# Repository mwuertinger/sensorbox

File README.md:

# Sensorbox

ESP8266 powered CO2, temperature, humidity and pressure sensor.

Displays the measurements on an OLED display and shows CO2 levels with green, yellow and red LEDs.
Measurements are sent via HTTPS to the [server](server/) which writes them to InfluxDB.
Alerting (temperature and battery) is handled by [temperature-alert](https://github.com/mwuertinger/temperature-alert).

## Software
The firmware is written in C++ and built using platformio. The server and config-tool are written in Go.

Generating protobuf code (required before building anything):
```
pip install nanopb==0.4.9.1 grpcio-tools
go install google.golang.org/protobuf/cmd/protoc-gen-go@latest
./protoc.sh
```

Building the firmware:
```
cd firmware
platformio run
```

Installing to a board connected via USB:
```
platformio run --target upload
```

### Configuration
The configuration is stored in flash and created with the [config-tool](config-tool/):
```
cd config-tool
go run ./generate -out config.bin -dev_id 1 -wlan_ssid ... -wlan_passwd ... -auth_token ... \
  -server_uri https://192.168.178.2:4000/sensorbox -server_fingerprint <sha1 of server cert> -bme280
esptool.py --port /dev/ttyUSB0 write_flash 0x03fb000 config.bin
```

The SHA1 fingerprint of the server certificate can be obtained with:
```
openssl x509 -in sensorbox-server.crt -noout -fingerprint -sha1
```
Devices with a fingerprint reject any other certificate, so reflash their config when the server certificate changes.

## Hardware
The PCB was designed with KiCad. The following parts are required:

### Parts
- 1x D1 Mini NodeMCU with ESP8266-12F
- 1x MH-Z14A NDIR CO2 Sensor
- 1x GY-BME280 Temperature/Humidity/Pressure Sensor
- 1x 128x64 Pixel 0.96in OLED Display with I2C Interface
- 3x LED
- 3x 2N7002 MOSFETs
- 3x 330Ω
- 2x 4.7kΩ
- 1x Button

### Pictures
#### Rendered PCB

#### PCB Front and Back

#### Assembled PCB

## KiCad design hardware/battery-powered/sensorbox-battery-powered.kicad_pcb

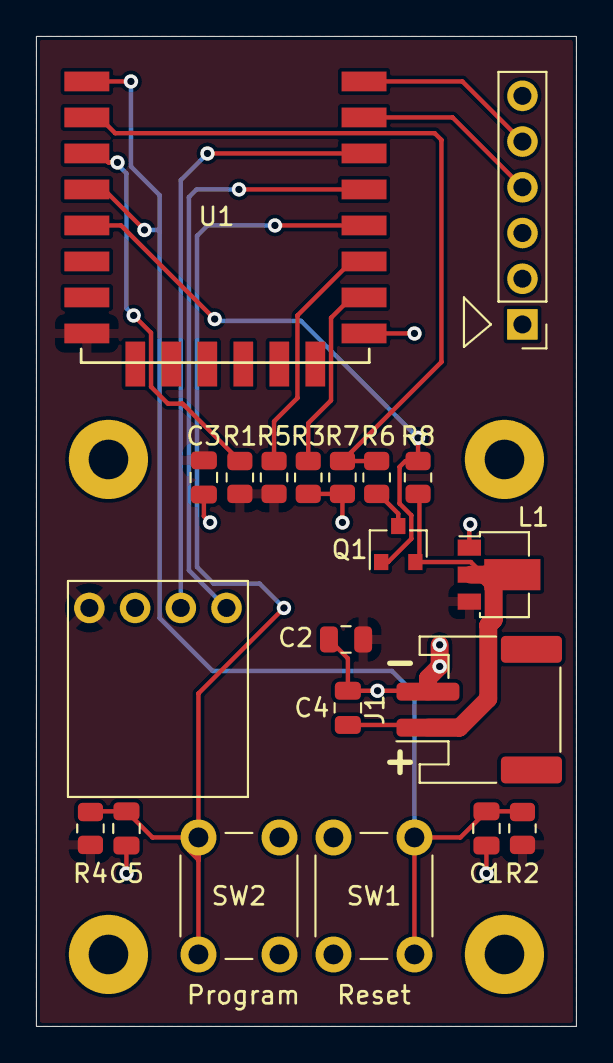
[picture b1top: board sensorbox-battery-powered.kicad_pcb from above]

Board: 2 copper layers, 30.0 x 55.0 mm, 21 parts (0 on the bottom side), 15 nets.

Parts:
C1, C3, C5: 100nF; C_0805_2012Metric
C2, C4: 10uF; C_0805_2012Metric
J1: Conn_01x02; JST_PH_S2B-PH-SM4-TB_1x02-1MP_P2.00mm_Horizontal
J2: Conn_01x06_Male; PinHeader_1x06_P2.54mm_Vertical
L1: HT7333-A; SOT-89-3
Q1: AO3401A; SOT-23
R1, R2, R3, R4, R5, R7, R8: 10k; R_0805_2012Metric
R6: 33k; R_0805_2012Metric
SW1: Reset; SW_PUSH_6mm
SW2: Program; SW_PUSH_6mm
U1: ESP-12F; ESP-12E_SMD
U2: BME280

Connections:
+3.3V: C2.1, C3.1, L1.3 (VOUT), R1.2, R2.2, R4.1, R5.1, U1.8 (VCC), U2.1 (VIN)
+BATT: C4.1, J1.1, L1.2 (VIN), Q1.2 (S), R8.1
BAT_SENS: R6.2, R7.1, U1.2 (ADC)
ENABLE_BAT_SENS: Q1.1 (G), R8.2, U1.5 (GPIO14)
GND: C1.1, C2.2, C3.2, C4.2, C5.1, J1.2, J2.1, L1.1 (GND), R3.1, R7.2, SW1.1, SW2.2, U1.9 (GND), U2.2 (GND)
unnamed: C1.2, R2.1, SW1.2, U1.1 (REST), U1.4 (GPIO16)
unnamed: C5.2, R4.2, SW2.1, U1.12 (GPIO0)
unnamed: J2.4, U1.15 (RXD)
unnamed: J2.5, U1.16 (TXD)
unnamed: Q1.3 (D), R6.1
unnamed: R1.1, U1.3 (CH_PD)
unnamed: R3.2, U1.10 (GPIO15)
unnamed: R5.2, U1.11 (GPIO2)
SCL: U1.14 (GPIO5), U2.3 (SCL)
SDA: U1.13 (GPIO4), U2.4 (SDA)

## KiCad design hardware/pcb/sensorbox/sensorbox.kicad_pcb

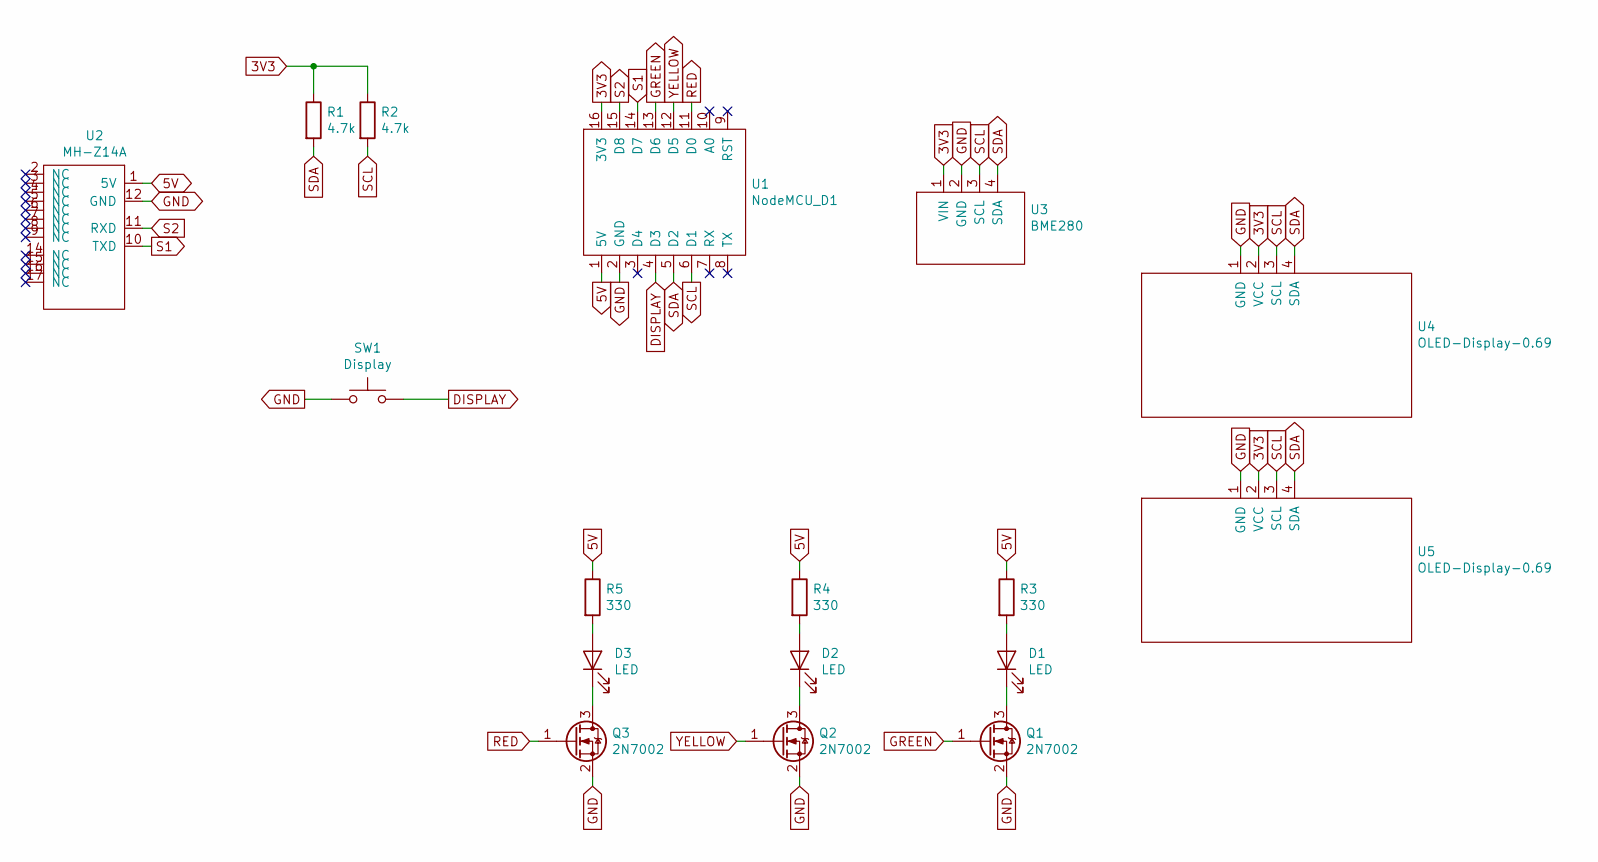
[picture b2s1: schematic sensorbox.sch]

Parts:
D1, D2, D3: LED; LED_D3.0mm
Q1, Q2, Q3: 2N7002; SOT-23
R1, R2: 4.7k; R_0805_2012Metric
R3, R4, R5: 330; R_0805_2012Metric
SW1: Display; SW_PUSH_6mm
U1: NodeMCU_D1
U2: MH-Z14A
U3: BME280
U4, U5: OLED-Display-0.69

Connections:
3V3: R1.1, R2.1, U1.16 (3V3), U3.1 (VIN), U4.2 (VCC), U5.2 (VCC)
5V: R3.1, R4.1, R5.1, U1.1 (5V), U2.1 (5V)
DISPLAY: SW1.2, U1.4 (D3)
GND: Q1.2 (S), Q2.2 (S), Q3.2 (S), SW1.1, U1.2 (GND), U2.12 (GND), U3.2 (GND), U4.1 (GND), U5.1 (GND)
GREEN: Q1.1 (G), U1.13 (D6)
unnamed: D1.1 (K), Q1.3 (D)
unnamed: D1.2 (A), R3.2
unnamed: D2.1 (K), Q2.3 (D)
unnamed: D2.2 (A), R4.2
unnamed: D3.1 (K), Q3.3 (D)
unnamed: D3.2 (A), R5.2
RED: Q3.1 (G), U1.11 (D0)
S1: U1.14 (D7), U2.10 (TXD)
S2: U1.15 (D8), U2.11 (RXD)
SCL: R2.2, U1.6 (D1), U3.3 (SCL), U4.3 (SCL), U5.3 (SCL)
SDA: R1.2, U1.5 (D2), U3.4 (SDA), U4.4 (SDA), U5.4 (SDA)
YELLOW: Q2.1 (G), U1.12 (D5)

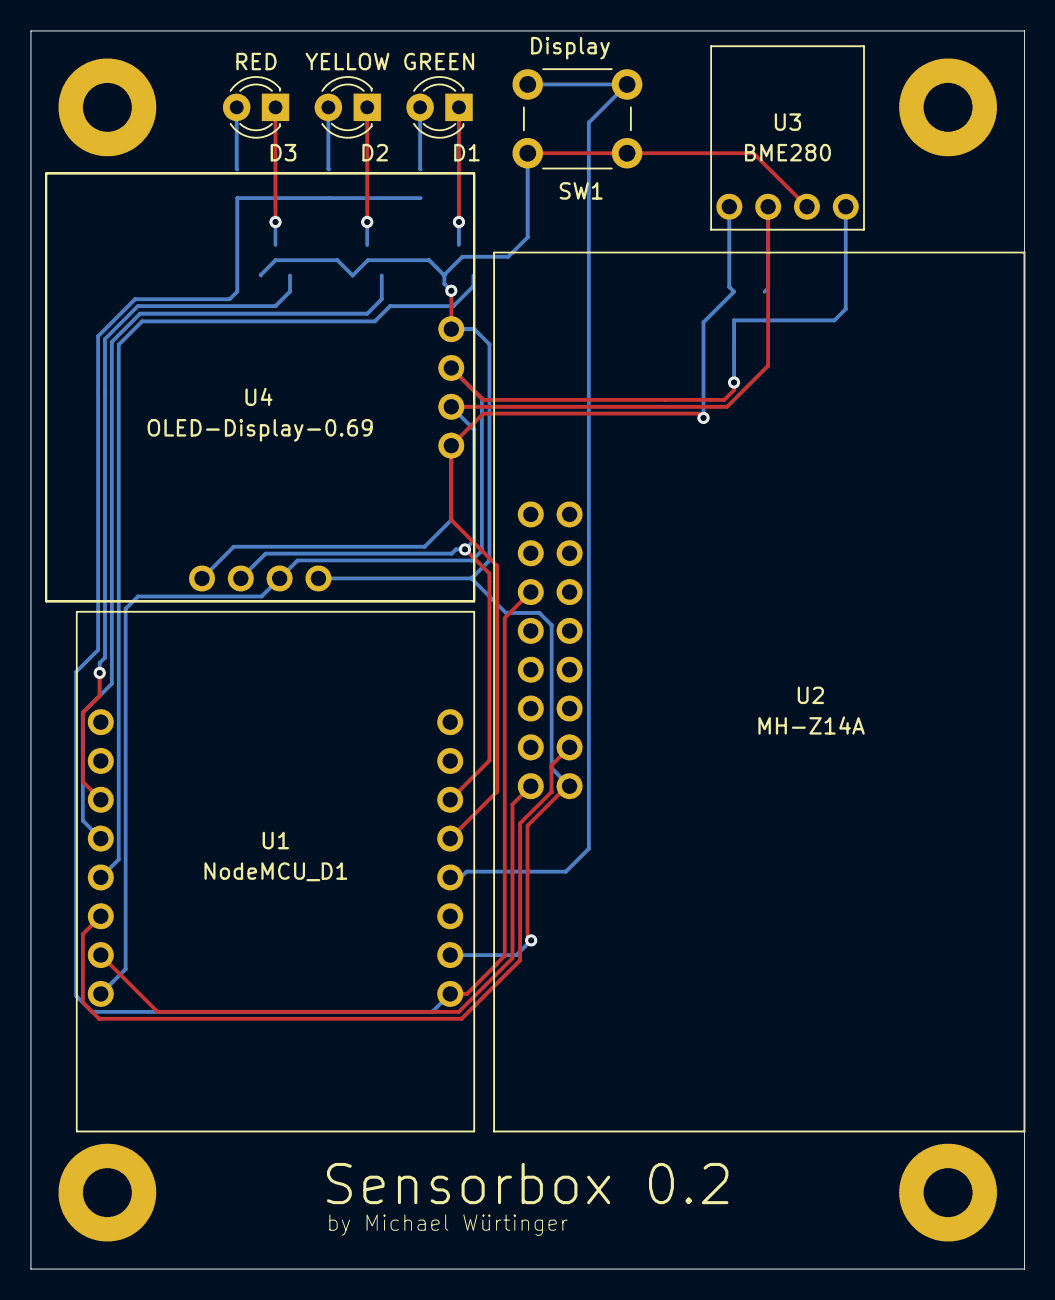
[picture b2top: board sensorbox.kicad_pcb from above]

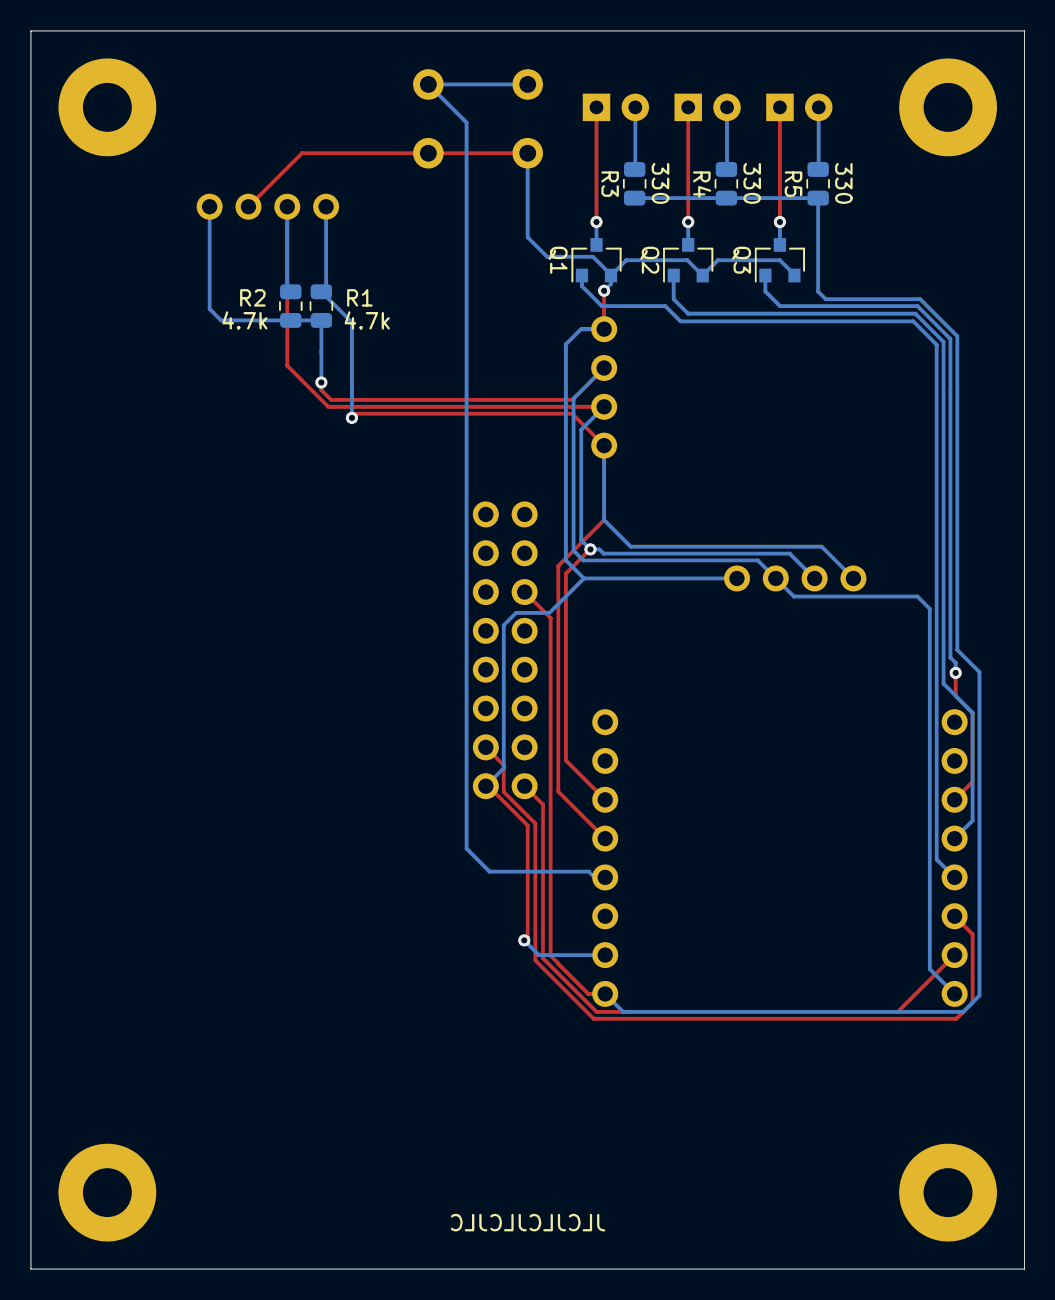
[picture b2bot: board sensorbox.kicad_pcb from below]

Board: 2 copper layers, 65.0 x 81.0 mm, 17 parts (8 on the bottom side), 17 nets.

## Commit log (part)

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2020-03-13 Initialized platformio
2020-03-13 Ported to PlatformIO
2020-03-13 CircleCI config
2020-03-13 Fix checkout
2020-03-13 Add platformio lib install
2020-03-13 Add empty credentials.h
2020-03-19 Add co2sensor code
2020-03-20 MQTT
    - Add MQTT implementation
    - Remove webserver
2020-03-20 Move code back to top level
    Move co2sensor to own repo: https://github.com/mwuertinger/co2sensor
2020-03-21 Remove unused import
2020-03-21 Reduce global variables
2020-03-21 Add CO2 sensor
2020-03-24 Error handling
2020-03-24 Remove TravisCI
2020-03-26 Switch to CSV encoding
    The MQTT library has a default message limit of 128 bytes. In order to
    keep messages within this limit it was necessary to switch to a more
    compact representation: CSV. In case this is still too large we could
    even switch to a binary representation.
    In addition the client name is replaced with a client ID to save some
    more space.
2020-03-26 Replace mqttClient with devId in Config
2020-05-22 CO2 measurement plausibility check
    Recently a sensorbox without connected CO2 sensor published a reading of
    26k. Apparently the ESP somehow read random data from the UART and the
    checksum matched by coincidence. To make this less likely implausible
    values are now discarded.
2020-10-11 Create software directory
2020-10-11 PCB Draft
2020-10-24 Final pcb design
2020-10-24 Add BOM and POS files
2020-10-29 Increased all hole sizes to 1mm
2020-11-08 LED and display implementation
2020-11-15 Implement dark mode
2020-11-27 Standardize soldering pad sizes and silk screens
2020-11-29 Board redesign
    - Move BME280 far away from MCU
    - Move display, LEDs and button next to each other
    - Rotate MCU to route cable out towards the bottom
2020-11-30 Optimize traces.
2020-12-01 Add name and author.
2020-12-01 Add order number placement label
2020-12-01 Generate new gerber files
2020-12-20 Fix build directory
2020-12-20 Add U8g2lib dependency
2020-12-20 Specify dependencies in platformio.ini
2020-12-20 Increase display font size.
2020-12-20 Remove CO2 sensor pre-heat delay
2020-12-20 Rename dark to display
2020-12-20 Trigger display button on RISING edge
2020-12-22 Add over the air update
2020-12-23 Add calibrate_co2 command and use hostname as topic
2020-12-31 Control display over MQTT.
    Enable/disable display via MQTT messages.
2020-12-31 Add README.md and pictures.
2020-12-31 Add picture headlines
2020-12-31 Add GPLv2 LICENSE
2021-03-06 Fix formatting
2021-03-06 Sort includes
2021-03-21 Config parsing and CRC
2021-03-21 Fix checksum offset
2021-03-26 Add carriage return to log message
2021-03-26 Remove static config
2021-03-26 Show hostname and IP address during initialization
2021-03-26 Put \r\n in the right order
2021-03-26 Rename software folder to firmware
2021-03-26 Use python:3.9.2-slim image
2021-03-26 Upgrade to platformio 5.1.1
2021-03-26 Add nanopb submodule
2021-03-26 Also build config-tool
2021-03-26 Add config-tool
2021-03-26 Use golang docker image
2021-12-19 Fix ESPhttpUpdate.
2022-01-04 Add script to generate protobuf files.
2022-01-04 Fix Go module path.
2022-01-04 Add README file.
2022-01-04 Add checksum verification.
2022-01-04 Add config-tool/pb to ignore list.
2022-01-04 Add all protoc generated files to ignore list.
2022-01-04 Support different sensorbox device combinations.
    New fields are added to the config to selectively enable/disable various devices
    which allows new types of sensorboxes.
2022-01-04 Remove generated files.
2022-01-04 Remove nanopb submodule.
    Nanopb is now used via OS package (eg. nanopb on Debian).
2022-01-04 Rename protoc.sh.
2022-01-04 Integrate protobuf compiler into platformio build.
2022-01-05 Fix CircleCI config.
    - Upgrade to latest Go image
    - Add nanopb dependency
    - Remove apt upgrade to make builds reproducible
2022-01-05 Use bullseye image in build.
2022-01-05 Fix nanopb arguments.
2022-01-05 Remove submodule initializtion from build script.
2022-01-05 Add spaces after arguments.
2022-01-05 Switch to platformio 5.2.4.
2022-01-05 Enable logging.
2022-01-05 Log working directory.
2022-07-04 Initial import.
2022-07-04 Fix courtyard.
2022-07-07 Add battery sensing circuit.
2022-07-07 Use SMD battery connector.
2022-07-11 Add basic server implementation.
2022-07-11 Final design.
2022-07-11 Add gerber abd BOM files.
2022-07-11 Add hardware sub-folder.
2022-07-11 Move .gitignore.
2022-07-11 Rename pcb to wired.
2022-07-13 Replace kicad-ESP8266 with submodule.
2022-07-24 Remove JST connectors libraries.
2022-08-16 Add sensorbox case design.
2022-08-19 Adjust code to support battery powered hardware.
    - Make LEDs optional
    - Add support for voltage measurements
    - Add support for deep sleep
2022-08-19 Use central protobuf compilation script.
2022-08-20 Add config, auth and InfluxDB support.
2022-08-30 Improve config, add testing and rename password to authToken.
2022-08-30 Use the configured listen address.
2022-08-30 Add test case for unknown device.
2022-08-30 Fix Go nanopb import issue.
2022-08-30 Code formatting.
2022-08-30 Remove NTP.
    We do not really have a use for wall clock time and querying it just
    drains the battery.
2022-09-03 Send data to HTTP endpoint.
    - Read server URI, fingerprint and authToken from config.
    - Divide sensorUpdate() into multiple smaller functions to make them
    more readable and to save stack space.
    - Add code to generate and send protobuf message.
    - Remove MQTT based code.
2022-12-31 Hardware cleanup.
2022-12-31 Fix LEDs and add LED-only mode.
    The new mode allows to turn off the display but keep the LEDs on.
2023-01-14 Fix test by using the right type.
2023-01-28 Add battery alert and opencensus and make client calls async.
2023-01-28 Add mutex to avoid race condition.
2023-01-29 Wait for goroutines to finish.
    Add a WaitGroup to properly wait for all goroutines to finish before
    termination to avoid data loss on server shutdown.
2023-01-29 Refactoring.
    - Rename app to application and h to app.
    - Rename s to server.
    - Extract processMeasurements() method.
2023-01-29 Move battery threshold voltage into config.
2023-02-12 Using qualified paths.
2023-02-12 Dependencies are now working.
2023-02-12 USe platformio_library.
2023-02-12 Fixed naming.
    Library must be called Adafruit_BME280, not adafruit_bme280 so that
    includes are named correctly.
2025-01-12 Upgrade to golang.org/x/net v0.34.0.
    Fixes CVE-2024-45338.
2025-01-12 Upgrade google.golang.org/protobuf to v1.33.0.
    Fixes CVE-2024-24786.
